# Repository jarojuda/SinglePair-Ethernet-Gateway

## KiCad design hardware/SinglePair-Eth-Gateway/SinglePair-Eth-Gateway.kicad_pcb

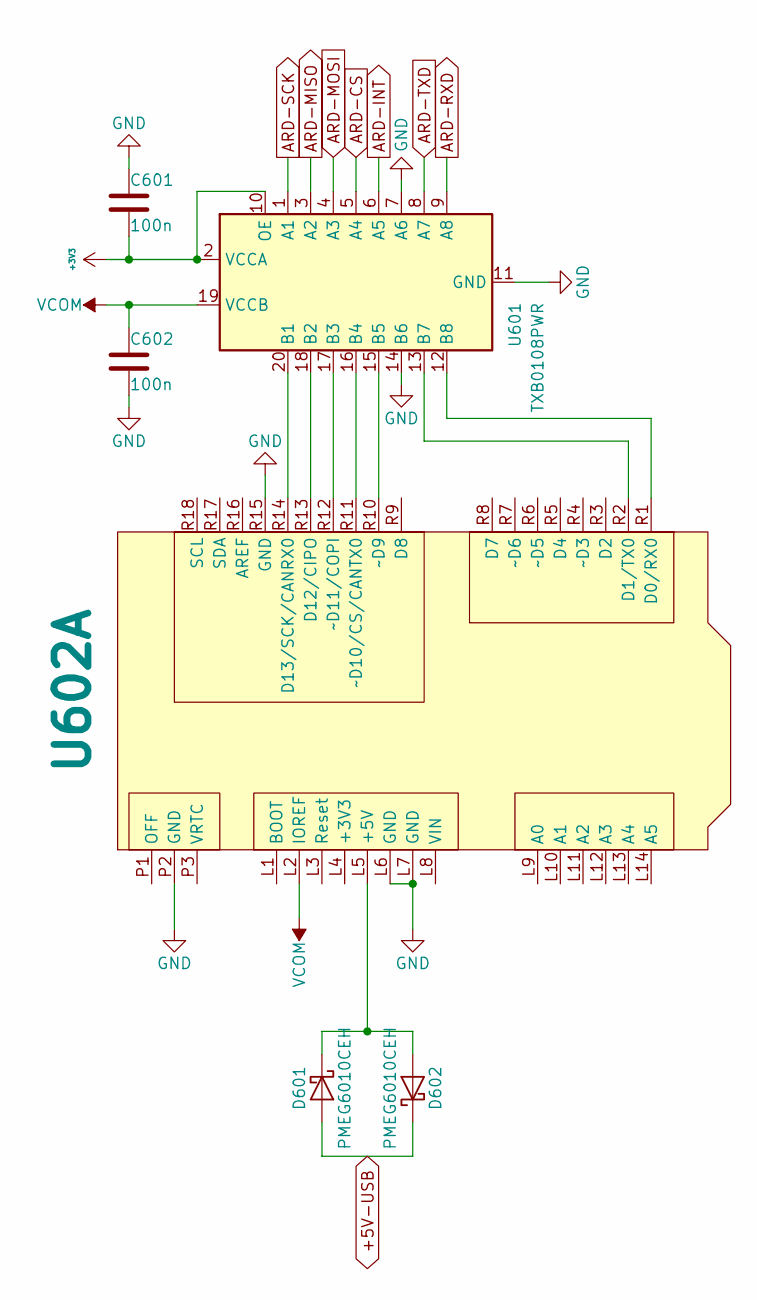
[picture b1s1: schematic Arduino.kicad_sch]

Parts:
C601, C602: 100n; C_0603_1608Metric
D601, D602: PMEG6010CEH; D_SOD-123F
U601: TXB0108PWR; TSSOP-20_4.4x6.5mm_P0.65mm
U602: Arduino_UNO_3_Connectors

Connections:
+3V3: C601.2, U601.2 (VCCA), U601.10 (OE); also elsewhere on the board
+5V-USB: D601.2 (A), D602.1 (K); also elsewhere on the board
ARD-CS: U601.5 (A4); also elsewhere on the board
ARD-INT: U601.6 (A5); also elsewhere on the board
ARD-MISO: U601.3 (A2); also elsewhere on the board
ARD-MOSI: U601.4 (A3); also elsewhere on the board
ARD-RXD: U601.9 (A8); also elsewhere on the board
ARD-SCK: U601.1 (A1); also elsewhere on the board
ARD-TXD: U601.8 (A7); also elsewhere on the board
GND: C601.1, C602.2, U601.7 (A6), U601.11 (GND), U601.14 (B6), U602.L6 (GND), U602.L7 (GND), U602.P2 (GND), U602.R15 (GND); also elsewhere on the board
unnamed: D601.1 (K), D602.2 (A), U602.L5 (+5V)
unnamed: U601.20 (B1), U602.R14 (D13/SCK/CANRX0)
unnamed: U601.18 (B2), U602.R13 (D12/CIPO)
unnamed: U601.17 (B3), U602.R12 (~D11/COPI)
unnamed: U601.16 (B4), U602.R11 (~D10/CS/CANTX0)
unnamed: U601.15 (B5), U602.R10 (~D9)
unnamed: U601.13 (B7), U602.R2 (D1/TX0)
unnamed: U601.12 (B8), U602.R1 (D0/RX0)
VCOM: C602.1, U601.19 (VCCB), U602.L2 (IOREF)

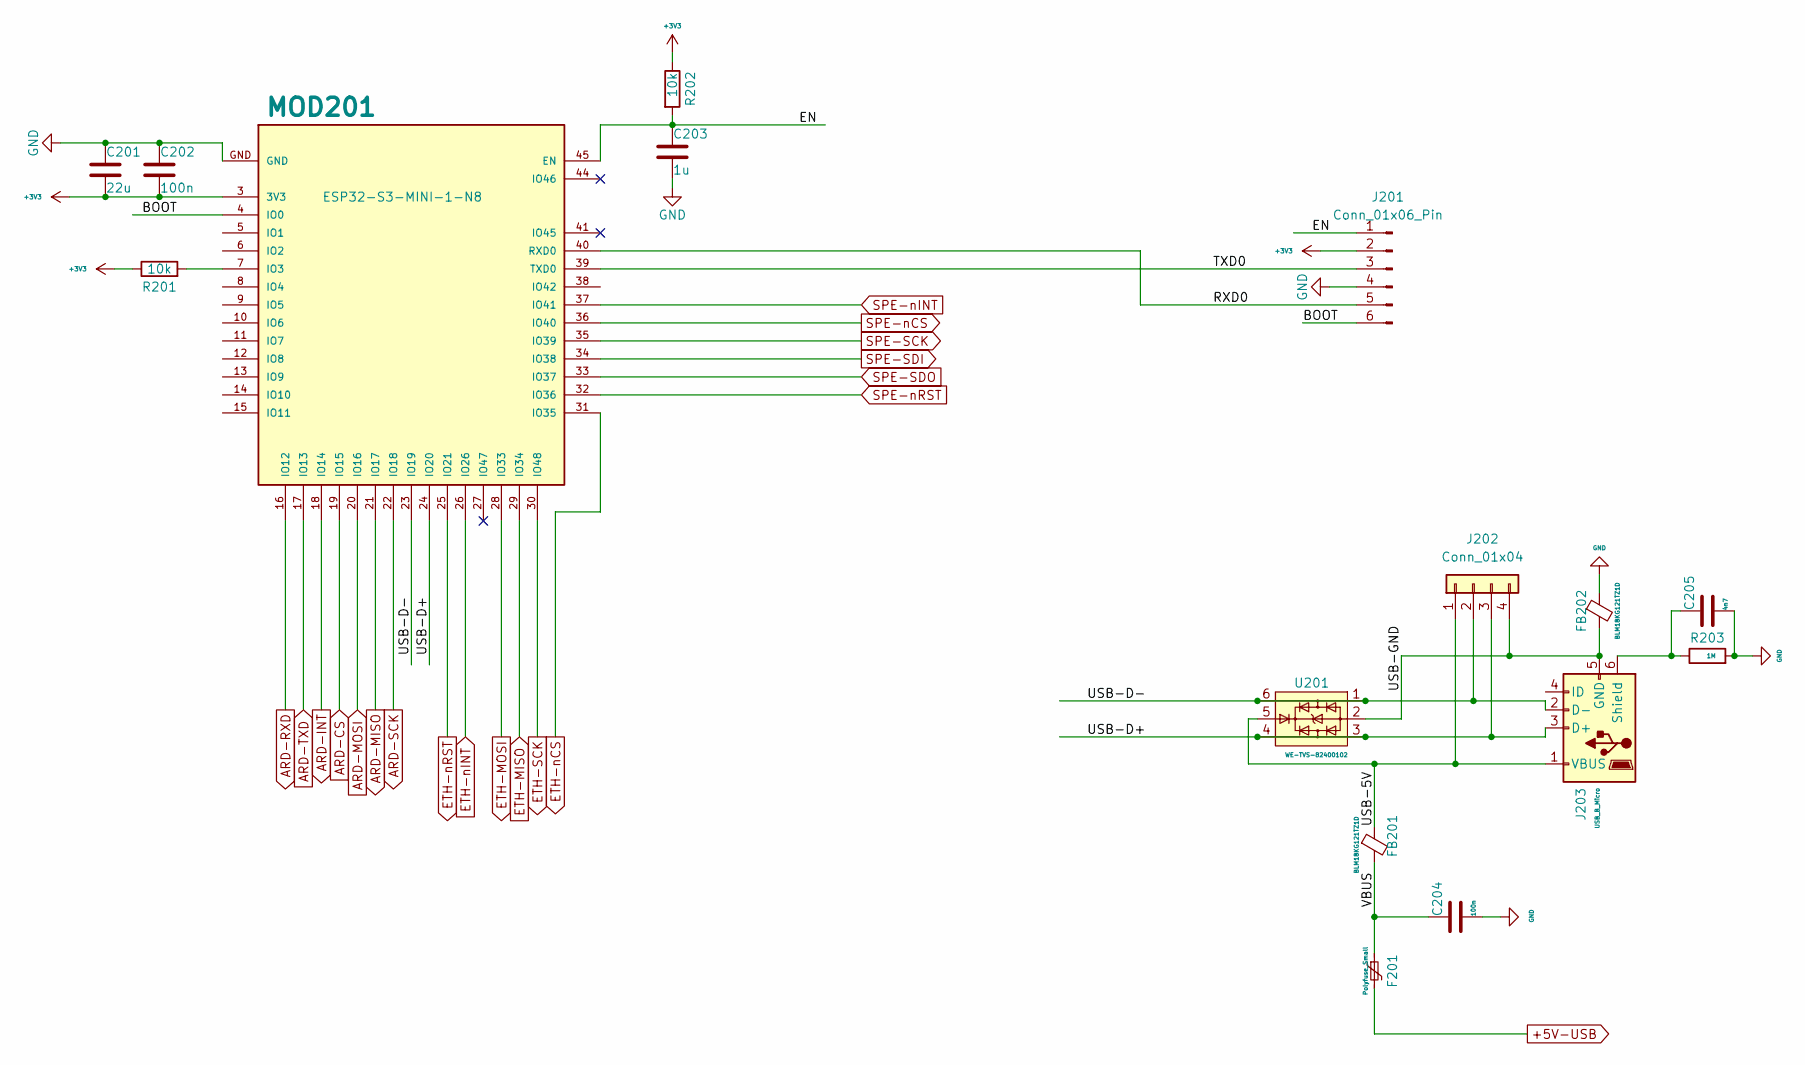
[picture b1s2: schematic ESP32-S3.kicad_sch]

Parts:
C201: 22u; C_0805_2012Metric
C202, C204: 100n; C_0603_1608Metric
C203: 1u; C_0603_1608Metric
C205: 4n7; C_0603_1608Metric
F201: Polyfuse_Small; Fuse_1210_3225Metric
FB201, FB202: BLM18KG121TZ1D; FB_0603_1608Metric
J201: Conn_01x06_Pin; PinHeader_1x06_P2.54mm_Vertical_SMD_Pin1Left
J202: Conn_01x04; PinSocket_1x04_P2.54mm_Vertical_SMD_Pin1Right
J203: USB_B_Micro; USB_Micro-B_Molex-105133-0001
MOD201: ESP32-S3-MINI-1-N8; XCVR_ESP32-S3-MINI-1-N8
R201, R202: 10k; R_0603_1608Metric
R203: 1M; R_0603_1608Metric
U201: WE-TVS-82400102; SOT-23-6

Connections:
+3V3: C201.2, C202.2, J201.2, MOD201.3 (3V3), R201.1, R202.1; also elsewhere on the board
+5V-USB: F201.2; also elsewhere on the board
/ESP32-S3/BOOT: J201.6, MOD201.4 (IO0)
/ESP32-S3/EN: C203.1, J201.1, MOD201.45 (EN), R202.2
/ESP32-S3/RXD0: J201.5, MOD201.40 (RXD0)
/ESP32-S3/TXD0: J201.3, MOD201.39 (TXD0)
/ESP32-S3/USB-5V: FB201.1, J202.1, J203.1 (VBUS), U201.5
/ESP32-S3/USB-D+: J202.3, J203.3 (D+), MOD201.24 (IO20), U201.3, U201.4
/ESP32-S3/USB-D-: J202.2, J203.2 (D-), MOD201.23 (IO19), U201.1, U201.6
/ESP32-S3/USB-GND: FB202.2, J202.4, J203.5 (GND), U201.2
/ESP32-S3/VBUS: C204.1, F201.1, FB201.2
ARD-CS: MOD201.19 (IO15); also elsewhere on the board
ARD-INT: MOD201.18 (IO14); also elsewhere on the board
ARD-MISO: MOD201.21 (IO17); also elsewhere on the board
ARD-MOSI: MOD201.20 (IO16); also elsewhere on the board
ARD-RXD: MOD201.16 (IO12); also elsewhere on the board
ARD-SCK: MOD201.22 (IO18); also elsewhere on the board
ARD-TXD: MOD201.17 (IO13); also elsewhere on the board
ETH-MISO: MOD201.29 (IO34); also elsewhere on the board
ETH-MOSI: MOD201.28 (IO33); also elsewhere on the board
ETH-SCK: MOD201.30 (IO48); also elsewhere on the board
ETH-nCS: MOD201.31 (IO35); also elsewhere on the board
ETH-nINT: MOD201.26 (IO26); also elsewhere on the board
ETH-nRST: MOD201.25 (IO21); also elsewhere on the board
GND: C201.1, C202.1, C203.2, C204.2, C205.2, FB202.1, J201.4, MOD201.GND, R203.2; also elsewhere on the board
unnamed: C205.1, J203.6 (Shield), R203.1
unnamed: MOD201.7 (IO3), R201.2
SPE-SCK: MOD201.35 (IO39); also elsewhere on the board
SPE-SDI: MOD201.34 (IO38); also elsewhere on the board
SPE-SDO: MOD201.33 (IO37); also elsewhere on the board
SPE-nCS: MOD201.36 (IO40); also elsewhere on the board
SPE-nINT: MOD201.37 (IO41); also elsewhere on the board
SPE-nRST: MOD201.32 (IO36); also elsewhere on the board

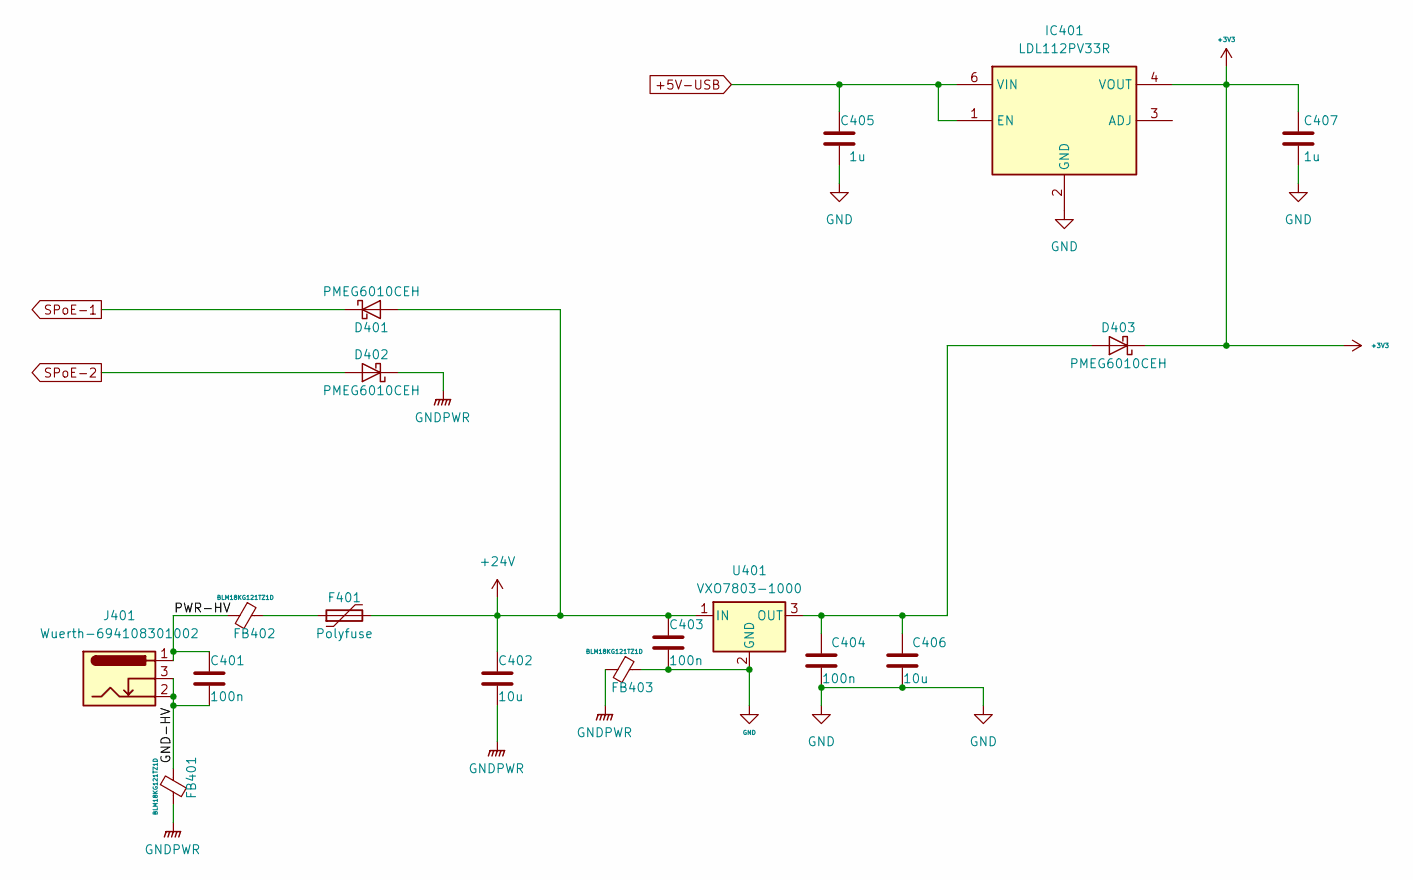
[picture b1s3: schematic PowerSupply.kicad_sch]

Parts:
C401, C403, C404: 100n; C_0603_1608Metric
C402, C406: 10u; C_0805_2012Metric
C405, C407: 1u; C_0603_1608Metric
D401, D402, D403: PMEG6010CEH; D_SOD-123F
F401: Polyfuse; Fuse_1210_3225Metric
FB401, FB402, FB403: BLM18KG121TZ1D; FB_0603_1608Metric
IC401: LDL112PV33R; SON95P300X300X100-7N-D; Manufacturer_Part_Number LDL112PV33R; Mouser Part Number 511-LDL112PV33R
J401: Wuerth-694108301002; BarrelJack_Wuerth_6941xx301002
U401: VXO7803-1000; TO-220-3_Vertical

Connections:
+3V3: C407.1, D403.1 (K), IC401.4 (VOUT); also elsewhere on the board
+5V-USB: C405.1, IC401.1 (EN), IC401.6 (VIN); also elsewhere on the board
+24V: C402.1, C403.1, D401.2 (A), F401.2, U401.1 (IN)
/PowerSupply/GND-HV: C401.2, FB401.1, J401.2, J401.3
/PowerSupply/PWR-HV: C401.1, FB402.2, J401.1
GND: C403.2, C404.2, C405.2, C406.2, C407.2, FB403.1, IC401.2 (GND), IC401.7 (EP), U401.2 (GND); also elsewhere on the board
GNDPWR: C402.2, D402.1 (K), FB401.2, FB403.2; also elsewhere on the board
unnamed: C404.1, C406.1, D403.2 (A), U401.3 (OUT)
unnamed: F401.1, FB402.1
SPoE-1: D401.1 (K); also elsewhere on the board
SPoE-2: D402.2 (A); also elsewhere on the board

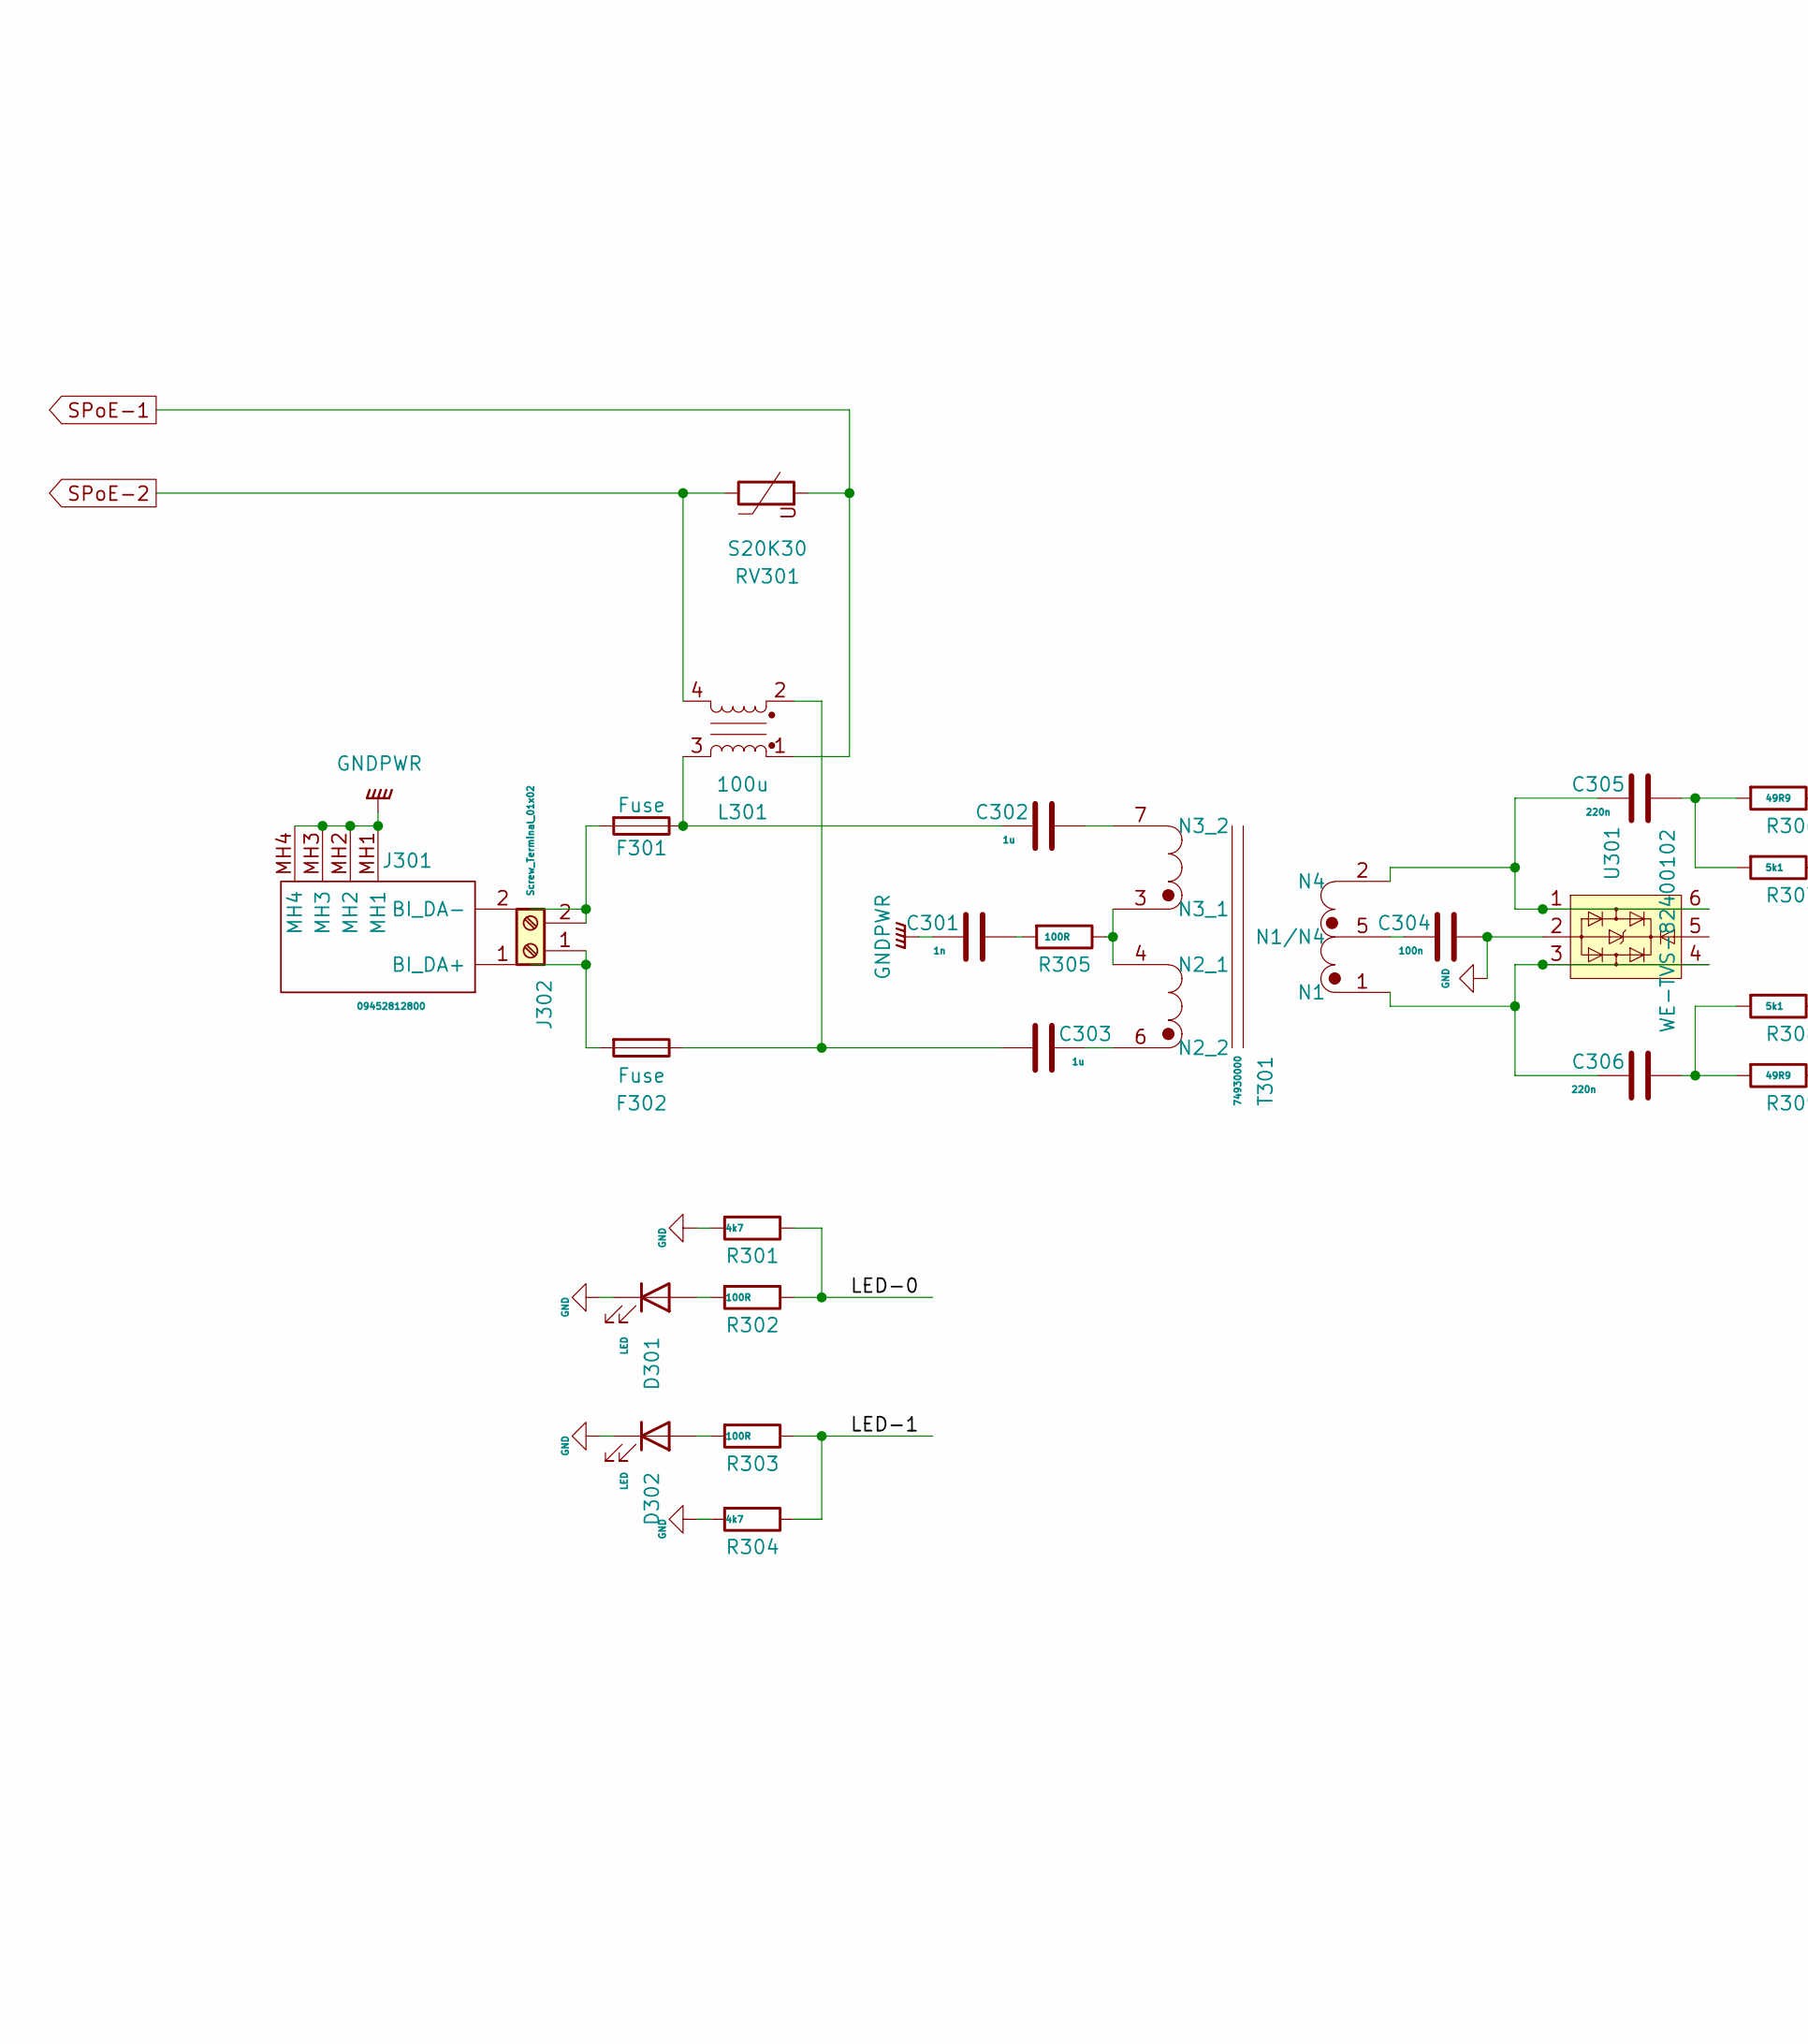
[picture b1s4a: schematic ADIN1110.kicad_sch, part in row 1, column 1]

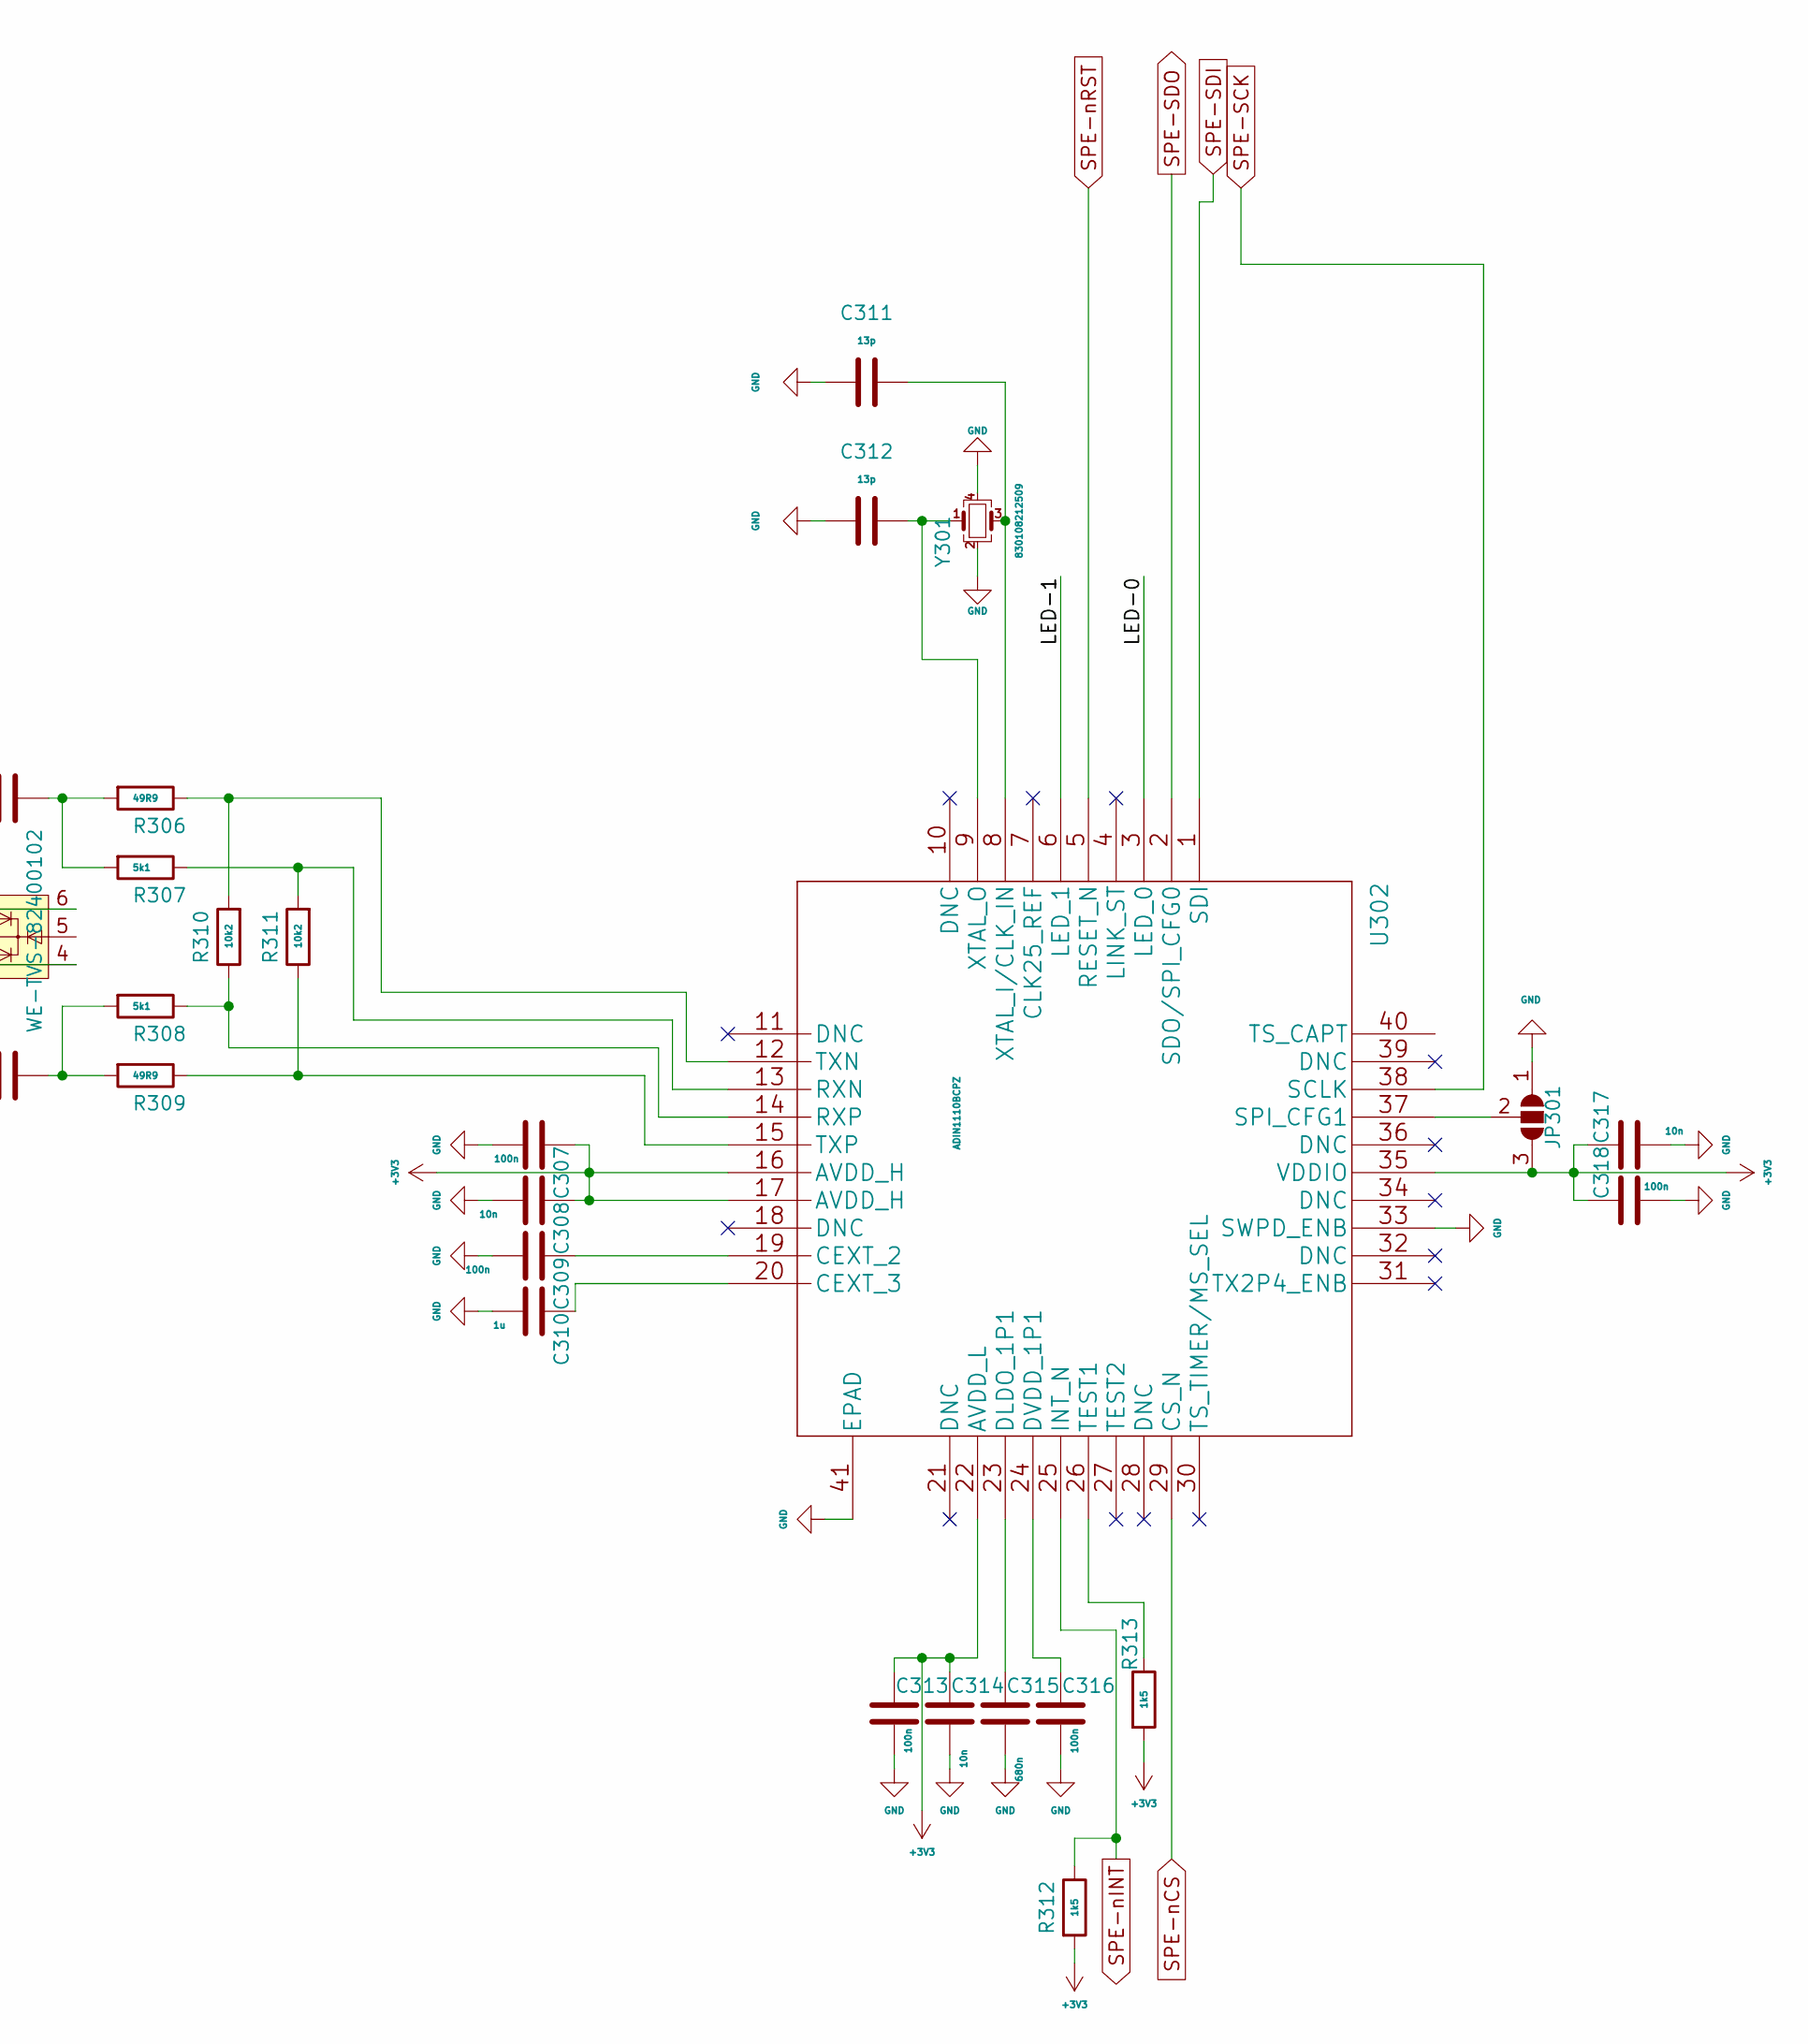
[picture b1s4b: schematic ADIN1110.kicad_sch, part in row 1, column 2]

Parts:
C301: 1n; C_1206_3216Metric
C302, C303, C310: 1u; C_0603_1608Metric
C304, C307, C309, C313, C316, C318: 100n; C_0603_1608Metric
C305, C306: 220n; C_0603_1608Metric
C308, C314, C317: 10n; C_0603_1608Metric
C311, C312: 13p; C_0603_1608Metric
C315: 680n; C_0603_1608Metric
D301, D302: LED; LED_0603_1608Metric
F301, F302: Fuse; Fuseholder_Cylinder-5x20mm_Schurter_0031_8201_Horizontal_Op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
J301: 09452812800; Manufacturer_Part_Number 09452812800; Mouser Part Number 617-09452812800
J302: Screw_Terminal_01x02; TerminalBlock_Altech_AK300-2_P5.00mm
JP301: SolderJumper_3_Open; SolderJumper-3_P1.3mm_Open_RoundedPad1.0x1.5mm
L301: 100u; 744871101
R301, R304: 4k7; R_0603_1608Metric
R302, R303, R305: 100R; R_0603_1608Metric
R306, R309: 49R9; R_0603_1608Metric
R307, R308: 5k1; R_0603_1608Metric
R310, R311: 10k2; R_0603_1608Metric
R312, R313: 1k5; R_0603_1608Metric
RV301: S20K30; RV_Disc_D21.5mm_W4.3mm_P10mm
T301: 74930000; Manufacturer_Part_Number 74930000; Mouser Part Number 710-74930000
U301: WE-TVS-82400102; SOT-23-6
U302: ADIN1110BCPZ; ADIN1110
Y301: 830108212509; Crystal_SMD_2016-4Pin_2.0x1.6mm

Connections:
+3V3: C307.1, C308.1, C313.1, C314.1, C317.1, C318.1, JP301.3 (B), R312.2, R313.2, U302.16 (AVDD_H), U302.17 (AVDD_H), U302.22 (AVDD_L), U302.35 (VDDIO); also elsewhere on the board
/ADIN1110/LED-0: R301.1, R302.1, U302.3 (LED_0)
/ADIN1110/LED-1: R303.1, R304.1, U302.6 (LED_1)
GND: C304.1, C307.2, C308.2, C309.2, C310.2, C311.1, C312.2, C313.2, C314.2, C315.2, C316.2, C317.2, C318.2, D301.1 (K), D302.1 (K), JP301.1 (A), R301.2, R304.2, U301.2, U302.33 (SWPD_ENB), U302.41 (EPAD), Y301.2, Y301.4; also elsewhere on the board
GNDPWR: C301.2, J301.MH1, J301.MH2, J301.MH3, J301.MH4; also elsewhere on the board
unnamed: C301.1, R305.2
unnamed: C302.2, F301.1, L301.3
unnamed: C303.1, F302.1, L301.2
unnamed: C305.1, R306.2, R307.2
unnamed: C306.2, R308.2, R309.2
unnamed: D301.2 (A), R302.2
unnamed: D302.2 (A), R303.2
unnamed: F302.2, J301.1 (BI_DA+), J302.1
unnamed: F301.2, J301.2 (BI_DA-), J302.2
unnamed: JP301.2 (C), U302.37 (SPI_CFG1)
unnamed: C306.1, T301.1 (N1), U301.3, U301.4
unnamed: C304.2, T301.5 (N1/N4)
unnamed: R305.1, T301.3 (N3_1), T301.4 (N2_1)
unnamed: C303.2, T301.6 (N2_2)
unnamed: C302.1, T301.7 (N3_2)
unnamed: C305.2, T301.2 (N4), U301.1, U301.6
unnamed: C309.1, U302.19 (CEXT_2)
unnamed: C310.1, U302.20 (CEXT_3)
unnamed: C315.1, U302.23 (DLDO_1P1)
unnamed: C316.1, U302.24 (DVDD_1P1)
unnamed: R307.1, R311.2, U302.13 (RXN)
unnamed: R308.1, R310.1, U302.14 (RXP)
unnamed: R313.1, U302.26 (TEST1)
unnamed: R306.1, R310.2, U302.12 (TXN)
unnamed: R309.1, R311.1, U302.15 (TXP)
unnamed: C311.2, U302.8 (XTAL_I/CLK_IN), Y301.3
unnamed: C312.1, U302.9 (XTAL_O), Y301.1
SPE-SCK: U302.38 (SCLK); also elsewhere on the board
SPE-SDI: U302.1 (SDI); also elsewhere on the board
SPE-SDO: U302.2 (SDO/SPI_CFG0); also elsewhere on the board
SPE-nCS: U302.29 (CS_N); also elsewhere on the board
SPE-nINT: R312.1, U302.25 (INT_N); also elsewhere on the board
SPE-nRST: U302.5 (RESET_N); also elsewhere on the board
SPoE-1: L301.1, RV301.2; also elsewhere on the board
SPoE-2: L301.4, RV301.1; also elsewhere on the board
